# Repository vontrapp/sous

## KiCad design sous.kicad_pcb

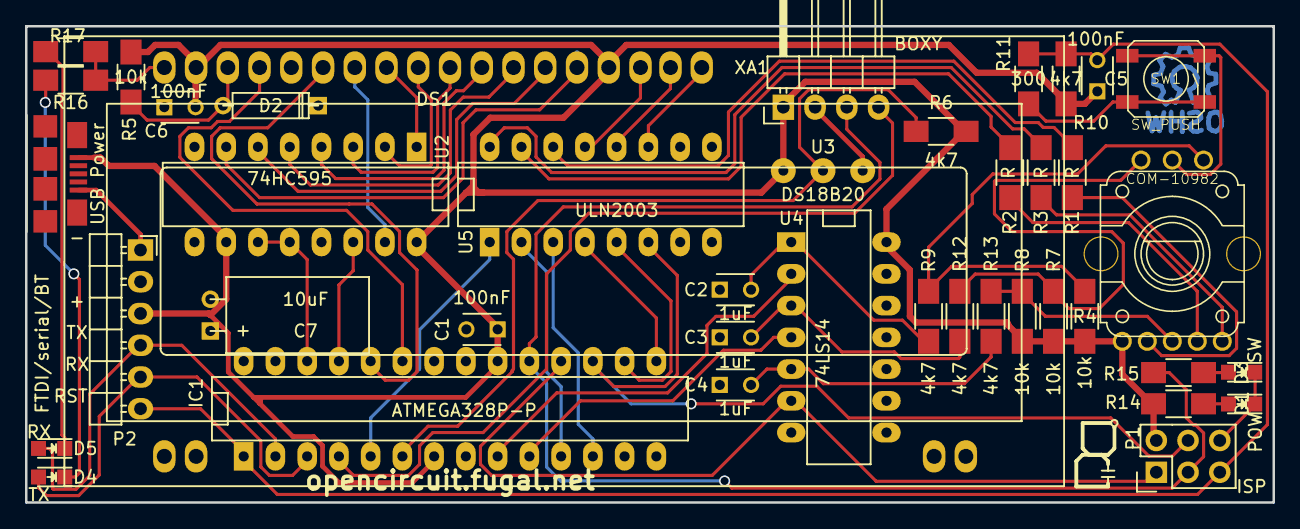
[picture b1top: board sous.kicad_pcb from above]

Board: 2 copper layers, 99.8 x 38.1 mm, 41 parts (0 on the bottom side), 50 nets.

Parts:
C1, C5, C6: 100nF; C_Disc_D3_P2.5
C2, C3, C4: 1uF; C_Disc_D3_P2.5
C7: 10uF; C1V5H
CON1: USB Power; USB_Micro
D1: POW; LED_0805
D2: D; D3
D3: SW; LED_0805
D4: TX; LED_0805
D5: RX; LED_0805
DS1: LCD16X2_RGB; WC1602A_RGB_Support
IC1: ATMEGA328P-P; DIP-28__300_ELL
P1: ISP; Pin_Header_Straight_2x03
P2: FTDI/serial/BT; Pin_Header_Angled_1x06_reverse
R1, R2, R3: R; R_1206_HandSoldering
R4, R5, R7, R8: 10k; R_1206_HandSoldering
R6, R9, R10, R12, R13: 4k7; R_1206_HandSoldering
R11: 300; R_1206_HandSoldering
R14: Power; R_1206_HandSoldering
R15: Switch; R_1206_HandSoldering
R16: RX; R_1206_HandSoldering
R17: TX; R_1206_HandSoldering
SW1: SW_PUSH; AB2_PB_MOM_5.2MM_SMD
U1: COM-10982; Encoder_RGB
U2: 74HC595; DIP-16__300_ELL
U3: DS18B20; SolderWirePad_3x_0-8mmDrill
U4: 74LS14; DIP-14__300_ELL
U5: ULN2003; DIP-16__300_ELL
XA1: BOXY; Pin_Header_Angled_1x04

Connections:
+5V: C1.1, C5.1, C6.2, C7.1, CON1.1, DS1.2, DS1.15, IC1.7, IC1.20, P1.2, P2.3, R4.2, R5.2, R6.2, R7.2, R8.2, R10.1, R14.1, U1.5, U2.10, U2.16, U3.3, U4.14, XA1.1
/BL: IC1.12, U5.3
/Debounce/In1: R4.1, R9.1, U1.A
/Debounce/In2: R7.1, R12.1, U1.B
/Debounce/In3: R8.1, R13.1, U1.3
/Debounce/Out1: IC1.9, U4.2
/Debounce/Out2: IC1.10, U4.4
/GR: IC1.11, U5.2
/LCD_B: IC1.17, P1.4, U5.6
/LCD_G: IC1.16, U5.5
/LCD_R: IC1.15, U5.4
/MISO: IC1.18, P1.1, U4.6
/RD: IC1.5, U5.1
/RST: C5.2, IC1.1, P1.5, P2.6, R10.2, R11.1
/RX: D5.2, IC1.2, P2.4
/SCK: IC1.19, P1.3, R15.1, XA1.3
/TX: D4.2, IC1.3, P2.5
GND: C1.2, C2.1, C3.1, C4.1, C6.1, C7.2, CON1.5, D1.1, D2.1, D3.1, DS1.1, DS1.5, IC1.8, IC1.22, P1.6, P2.1, R16.1, R17.1, SW1.2, U1.C, U2.8, U2.13, U3.1, U4.7, U5.8, U5.9, XA1.2
unnamed: C2.2, R9.2, U4.1
unnamed: C3.2, R12.2, U4.3
unnamed: C4.2, R13.2, U4.5
unnamed: D1.2, R14.2
unnamed: D2.2, DS1.3, R5.1
unnamed: D3.2, R15.2
unnamed: D4.1, R16.2
unnamed: D5.1, R17.2
unnamed: DS1.4, IC1.23
unnamed: DS1.6, IC1.24
unnamed: DS1.7, U2.15
unnamed: DS1.8, U2.1
unnamed: DS1.9, U2.2
unnamed: DS1.10, U2.3
unnamed: DS1.11, U2.4
unnamed: DS1.12, U2.5
unnamed: DS1.13, U2.6
unnamed: DS1.14, U2.7
unnamed: DS1.16, U5.13
unnamed: DS1.17, U5.12
unnamed: DS1.18, U5.11
unnamed: IC1.4, XA1.4
unnamed: IC1.6, R6.1, U3.2
unnamed: IC1.25, U2.14
unnamed: IC1.26, U2.11, U2.12
unnamed: R1.1, U5.14
unnamed: R1.2, U1.4
unnamed: R2.1, U5.15
unnamed: R2.2, U1.2
unnamed: R3.1, U5.16
unnamed: R3.2, U1.1
unnamed: R11.2, SW1.1

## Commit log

2015-10-12 initial design submitted to dirtypcb
2015-10-12 shrink board to <10cm long
2016-09-04 Updated to newer kicad, fixed tx/rx swap
